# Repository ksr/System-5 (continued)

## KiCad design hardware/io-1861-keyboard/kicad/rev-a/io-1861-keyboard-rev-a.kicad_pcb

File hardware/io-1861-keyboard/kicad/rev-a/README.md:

# io-1861-keyboard-rev-a — KiCad conversion

Generated 2026-10-06 by `tools/eagle_to_kicad_all.py` from the Fusion XML export of the Eagle design `Video` in `hardware/io-1861-keyboard/eagle/rev-a/fusion-export/`. **The Eagle files are the record of what was designed and built; this KiCad project is derived from them and is regenerated from scratch on every run of the tool** (hand edits here will be lost - once a card is edited in KiCad, remove it from the tool's list). This revision was FABRICATED (see `hardware/FABRICATED.md`).

## Files

| File | What it is |
|---|---|
| `io-1861-keyboard-rev-a.kicad_pro` | project; DRC uses OSH Park rules (6 mil track, 5 mil clearance, 10 mil drill, 4 mil annular) as a modern-fab check, not the 2005 fab's rules |
| `io-1861-keyboard-rev-a.kicad_sch` | root sheet; 1 sub-sheet(s) `io-1861-keyboard-rev-a-sheetN.kicad_sch` mirror the Eagle sheets |
| `io-1861-keyboard-rev-a-eagle.kicad_sym` | project symbol library generated from the Eagle libraries used (units = Eagle gates) |
| `io-1861-keyboard-rev-a.kicad_pcb` | the board: 4 copper layers, 47 footprints, 999 track segments, 112 vias; 4 items on unmapped Eagle layers dropped |
| `io-1861-keyboard-rev-a-eagle.pretty/` | project footprint library extracted from the imported board |
| `reports/` | ERC (`erc.json`), DRC (`drc.json`), schematic PDF, board renders (`-top.png`, `-bottom.png`), netlist + `netlist-compare.txt` |

## Proof

Schematic-vs-board netlist comparison (`tools/kicad/compare_netlists.py`: every (reference, pad) partition must be identical): **MATCH (79/79 nets)**

```
  same connectivity, different net name: [('/Sheet 1/-INT', '-INT'), ('/Sheet 1/-MRD', '-MRD'), ('/Sheet 1/CLK', 'CLK'), ('/Sheet 1/DATA', 'DATA'), ('/Sheet 1/DATA0', 'DATA0'), ('/Sheet 1/DATA1', 'DATA1'), ('/Sheet 1/DATA2', 'DATA2'), ('/Sheet 1/DATA3', 'DATA3'), ('/Sheet 1/DATA4', 'DATA4'), ('/Sheet 1/DATA5', 'DATA5'), ('/Sheet 1/DATA6', 'DATA6'), ('/Sheet 1/DATA7', 'DATA7'), ('/Sheet 1/DMA_OUT', 'DMA_OUT'), ('/Sheet 1/EFK', 'EFK'), ('/Sheet 1/EFV', 'EFV'), ('/Sheet 1/IN', 'IN'), ('/Sheet 1/KD0', 'KD0'), ('/Sheet 1/KD1', 'KD1'), ('/Sheet 1/KD2', 'KD2'), ('/Sheet 1/KD3', 'KD3'), ('/Sheet 1/KD4', 'KD4'), ('/Sheet 1/KD5', 'KD5'), ('/Sheet 1/KD6', 'KD6'), ('/Sheet 1/KD7', 'KD7'), ('/Sheet 1/LCLK', 'LCLK'), ('/Sheet 1/N0', 'N0'), ('/Sheet 1/N1', 'N1'), ('/Sheet 1/N2', 'N2'), ('/Sheet 1/OUT', 'OUT'), ('/Sheet 1/PORT1', 'PORT1'), ('/Sheet 1/PORT2', 'PORT2'), ('/Sheet 1/PORT3', 'PORT3'), ('/Sheet 1/PORT4', 'PORT4'), ('/Sheet 1/PORT5', 'PORT5'), ('/Sheet 1/PORT6', 'PORT6'), ('/Sheet 1/PORT7', 'PORT7'), ('/Sheet 1/RESET', 'RESET'), ('/Sheet 1/SC0', 'SC0'), ('/Sheet 1/SC1', 'SC1'), ('/Sheet 1/TPA', 'TPA'), ('/Sheet 1/TPB', 'TPB'), ('Net-(IC1-OSC1)', 'N$19'), ('Net-(IC1-OSC2)', 'N$21'), ('Net-(IC1-RA0)', 'N$3'), ('Net-(IC1-RA1)', 'N$6'), ('Net-(IC1-RA2)', 'N$15'), ('Net-(IC2A-~{Q})', 'N$24'), ('Net-(IC11A-I)', 'N$5'), ('Net-(IC11A-O)', 'N$10'), ('Net-(IC11C-O)', 'N$28'), ('Net-(IC11D-O)', 'N$14'), ('Net-(IC11E-I)', 'N$41'), ('Net-(IC11E-O)', 'N$40'), ('Net-(IC11F-I)', 'N$20'), ('Net-(IC11F-O)', 'N$18'), ('Net-(IC13A-O)', 'N$11'), ('Net-(IC14A-I1)', 'N$13'), ('Net-(IC14A-O)', 'N$12'), ('Net-(IC14C-O)', 'N$26'), ('Net-(IC14D-O)', 'N$39'), ('Net-(IC16A-I1)', 'N$42'), ('Net-(IC16A-O)', 'N$43'), ('Net-(IC16B-O)', 'N$44'), ('Net-(LED1-C)', 'N$22'), ('Net-(LED2-C)', 'N$23'), ('Net-(LED3-C)', 'N$4'), ('Net-(LED4-C)', 'N$25'), ('Net-(LED5-C)', 'N$29'), ('Net-(R13-Pad1)', 'N$9'), ('Net-(U$1-SR)', 'N$16'), ('Net-(U$2--EF4)', 'N$17'), ('Net-(U$3-SYNC)', 'N$7'), ('Net-(U$3-VIDEO)', 'N$8'), ('Net-(U$5-DA)', 'N$27'), ('Net-(U$5-RES1)', 'N$1'), ('Net-(U$5-RES2)', 'N$2'), ('Net-(X1-PE1)', 'N$30')]
```

## Readability

`tools/kicad/sch_overlaps.py` over every sheet: text over text 3, text over a symbol body 6, text crossed by a line 2, items off the drawing frame or on the title block 0. What is left is mostly the Eagle drawing itself (parts placed that close in Eagle) or KiCad drawing pin numbers centred on short pins.

## Residual ERC / DRC

ERC by type: endpoint_off_grid 19, missing_input_pin 4, missing_power_pin 4, missing_unit 4, power_pin_not_driven 1, unconnected_wire_endpoint 17.
`isolated_pin_label` = the converter's per-net global labels (cosmetic); `power_pin_not_driven` / unused-unit notes are the same ones KiCad's own Eagle importer leaves. `unconnected_wire_endpoint` / `pin_not_connected` = wire stubs Eagle leaves bare (mostly net wires ending on a bus, which is drawn as graphics here); since 2026-09-23 the converter no longer hangs a label on every such end (that was most of the label clutter), so they show as KiCad warnings.

DRC by type: lib_footprint_mismatch 2, silk_edge_clearance 1, silk_over_copper 199, silk_overlap 22, text_height 6, text_thickness 6; unconnected items 0; schematic parity 0.
Silk-over-pad and clearance notes reflect the Eagle design as drawn; unconnected items are Eagle airwires (parts the design left unrouted).

Converter: converted: 80 symbols, 408 wires, 85 labels, 79 junctions, 5 bus lines, 27 no-connects

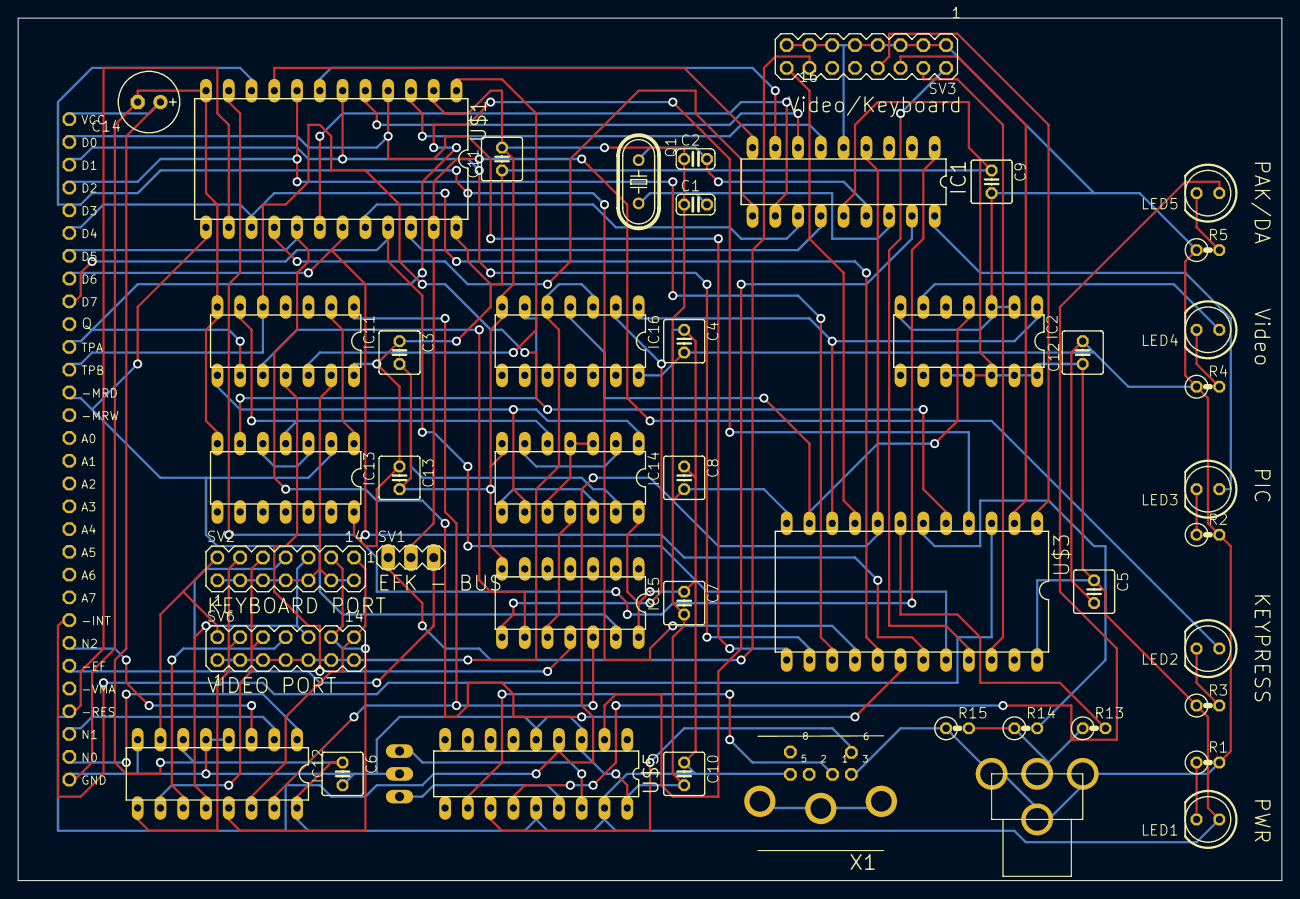
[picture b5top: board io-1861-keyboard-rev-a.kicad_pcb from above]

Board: 4 copper layers, 140.9 x 96.2 mm, 47 parts (0 on the bottom side), 79 nets.

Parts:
C1, C2: C025-024X044
C3, C4, C5, C6, C7, C8, C9, C10, C11, C12, C13: C025-050X050
C14: E2,5-7
IC1: PIC16F84AP; DIL18
IC2: 74LS74N; DIL14
IC11: 74LS04N; DIL14
IC12: 74LS138N; DIL16
IC13: 74S32N; DIL14
IC14, IC15: 74LS00N; DIL14
IC16: 74LS02N; DIL14
LED1, LED2, LED3, LED4, LED5: LED5MM
Q1: HC49U-V
R1, R2, R3, R4, R5, R13, R14, R15: 0207_2V
SV1: MA03-1
SV2, SV6: MA07-2
SV3: MA08-2
U$1: 1852; DIL24
U$2: C30
U$3: CDP1861; DIP24
U$4: RCA
U$5: PAKVI; DIL18
U$6: RESONATOR; MA03-1
X1: M_DIN6

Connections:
-INT: U$2.23, U$3.3
-MRD: IC13.2, IC15.13, U$1.13, U$2.13
CLK: U$5.12, X1.6
DATA: U$5.11, X1.1
DATA0: U$1.4, U$2.2, U$3.13
DATA1: U$1.6, U$2.3, U$3.14
DATA2: U$1.8, U$2.4, U$3.15
DATA3: U$1.10, U$2.5, U$3.16
DATA4: U$1.15, U$2.6, U$3.17
DATA5: U$1.17, U$2.7, U$3.18
DATA6: U$1.19, U$2.8, U$3.19
DATA7: U$1.21, U$2.9, U$3.20
DMA_OUT: SV3.6, U$3.2
EFK: SV1.1, SV3.14
EFV: SV3.16, U$3.9
GND: C1.1, C2.1, C3.2, C4.2, C5.2, C6.2, C7.2, C8.2, C9.2, C10.2, C11.2, C12.2, C13.2, C14.-, IC1.5, IC2.2, IC2.3, IC2.7, IC11.7, IC12.4, IC12.5, IC12.8, IC13.7, IC14.7, IC15.7, IC16.7, R1.2, R2.2, R4.1, R5.1, R15.1, SV3.1, SV3.3, SV3.5, SV3.7, SV3.9, SV3.11, SV3.13, SV3.15, U$1.2, U$1.12, U$2.30, U$3.12, U$4.S1, U$4.S2, U$4.S3, U$5.3, U$5.5, U$5.18, U$6.2, X1.3
IN: IC15.8, IC16.2
KD0: IC1.6, U$1.3
KD1: IC1.7, U$1.5
KD2: IC1.8, U$1.7
KD3: IC1.9, U$1.9
KD4: IC1.10, U$1.16
KD5: IC1.11, U$1.18
KD6: IC1.12, U$1.20
KD7: IC1.13, U$1.22
LCLK: SV3.8, U$3.1
N0: IC12.1, U$2.29
N1: IC12.2, U$2.28
N2: IC12.3, U$2.24
unnamed: U$5.15, U$6.3
unnamed: U$5.16, U$6.1
unnamed: IC1.17, U$5.2
unnamed: LED3.K, R2.1
unnamed: IC11.1, IC12.15, IC15.12
unnamed: IC1.18, LED3.A
unnamed: R14.2, U$3.6
unnamed: R13.2, U$3.7
unnamed: R13.1, R14.1, R15.2, U$4.C1
unnamed: IC11.2, IC13.1
unnamed: IC13.3, IC13.5
unnamed: IC14.3, IC14.4, IC14.10
unnamed: IC14.2, IC14.6
unnamed: IC11.8, IC14.1, IC14.9
unnamed: IC1.1, U$1.11
unnamed: LED2.A, SV1.2, U$1.23
unnamed: SV1.3, U$2.25
unnamed: IC11.12, U$1.1
unnamed: C1.2, IC1.16, Q1.2
unnamed: IC11.13, SV2.1, SV2.3, SV2.5, SV2.7, SV2.9, SV2.11, SV2.13
unnamed: C2.2, IC1.15, Q1.1
unnamed: LED1.K, R1.1
unnamed: LED2.K, R3.2
unnamed: IC2.6, LED4.A
unnamed: LED4.K, R4.2
unnamed: IC14.8, IC14.12
unnamed: LED5.A, U$5.13
unnamed: IC11.6, IC13.4, IC14.5, IC14.13
unnamed: LED5.K, R5.2
unnamed: X1.SH1, X1.SH2, X1.SH3
unnamed: IC14.11, IC15.10
unnamed: IC11.10, IC15.9
unnamed: IC11.11, IC15.11
unnamed: IC16.3, IC16.5, SV6.1, SV6.3, SV6.5, SV6.7, SV6.9, SV6.11, SV6.13
unnamed: IC2.1, IC16.1, U$3.10
unnamed: IC2.4, IC16.4, U$3.11
OUT: IC13.6, IC16.6
PORT1: IC12.14, SV2.14, SV6.14
PORT2: IC12.13, SV2.12, SV6.12
PORT3: IC12.12, SV2.10, SV6.10
PORT4: IC12.11, SV2.8, SV6.8
PORT5: IC12.10, SV2.6, SV6.6
PORT6: IC12.9, SV2.4, SV6.4
PORT7: IC12.7, SV2.2, SV6.2
RESET: IC1.4, U$1.14, U$2.27, U$3.8, U$5.4
SC0: SV3.2, U$3.21
SC1: SV3.4, U$3.22
TPA: IC11.9, U$2.11, U$3.4
TPB: IC11.5, U$2.12, U$3.5
VCC: C3.1, C4.1, C5.1, C6.1, C7.1, C8.1, C9.1, C10.1, C11.1, C12.1, C13.1, C14.+, IC1.14, IC2.10, IC2.11, IC2.12, IC2.13, IC2.14, IC11.14, IC12.6, IC12.16, IC13.14, IC14.14, IC15.14, IC16.14, LED1.A, R3.1, U$1.24, U$2.1, U$3.24, U$5.14, U$5.17, X1.5

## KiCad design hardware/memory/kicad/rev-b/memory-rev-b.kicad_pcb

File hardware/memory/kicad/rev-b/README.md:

# memory-rev-b — KiCad conversion

Generated 2026-10-05 by `tools/eagle_to_kicad_all.py` from the Fusion XML export of the Eagle design `mem3-b` in `hardware/memory/eagle/rev-b/fusion-export/`. **The Eagle files are the record of what was designed and built; this KiCad project is derived from them and is regenerated from scratch on every run of the tool** (hand edits here will be lost - once a card is edited in KiCad, remove it from the tool's list). This revision was FABRICATED (see `hardware/FABRICATED.md`).

## Files

| File | What it is |
|---|---|
| `memory-rev-b.kicad_pro` | project; DRC uses OSH Park rules (6 mil track, 5 mil clearance, 10 mil drill, 4 mil annular) as a modern-fab check, not the 2005 fab's rules |
| `memory-rev-b.kicad_sch` | root sheet; 1 sub-sheet(s) `memory-rev-b-sheetN.kicad_sch` mirror the Eagle sheets |
| `memory-rev-b-eagle.kicad_sym` | project symbol library generated from the Eagle libraries used (units = Eagle gates) |
| `memory-rev-b.kicad_pcb` | the board: 4 copper layers, 48 footprints, 1547 track segments, 170 vias; 2 items on unmapped Eagle layers dropped |
| `memory-rev-b-eagle.pretty/` | project footprint library extracted from the imported board |
| `reports/` | ERC (`erc.json`), DRC (`drc.json`), schematic PDF, board renders (`-top.png`, `-bottom.png`), netlist + `netlist-compare.txt` |

## Proof

Schematic-vs-board netlist comparison (`tools/kicad/compare_netlists.py`: every (reference, pad) partition must be identical): **MATCH (88/88 nets)**

```
  same connectivity, different net name: [('/Sheet 1/BUFFADDR0', 'BUFFADDR0'), ('/Sheet 1/BUFFADDR1', 'BUFFADDR1'), ('/Sheet 1/BUFFADDR2', 'BUFFADDR2'), ('/Sheet 1/BUFFADDR3', 'BUFFADDR3'), ('/Sheet 1/BUFFADDR4', 'BUFFADDR4'), ('/Sheet 1/BUFFADDR5', 'BUFFADDR5'), ('/Sheet 1/BUFFADDR6', 'BUFFADDR6'), ('/Sheet 1/BUFFADDR7', 'BUFFADDR7'), ('/Sheet 1/BUFFADDR8', 'BUFFADDR8'), ('/Sheet 1/BUFFADDR9', 'BUFFADDR9'), ('/Sheet 1/BUFFADDR10', 'BUFFADDR10'), ('/Sheet 1/BUFFADDR11', 'BUFFADDR11'), ('/Sheet 1/BUFFADDR12', 'BUFFADDR12'), ('/Sheet 1/BUFFADDR13', 'BUFFADDR13'), ('/Sheet 1/BUFFADDR14', 'BUFFADDR14'), ('/Sheet 1/BUFFADDR15', 'BUFFADDR15'), ('/Sheet 1/BUSDATA0', 'BUSDATA0'), ('/Sheet 1/BUSDATA1', 'BUSDATA1'), ('/Sheet 1/BUSDATA2', 'BUSDATA2'), ('/Sheet 1/BUSDATA3', 'BUSDATA3'), ('/Sheet 1/BUSDATA4', 'BUSDATA4'), ('/Sheet 1/BUSDATA5', 'BUSDATA5'), ('/Sheet 1/BUSDATA6', 'BUSDATA6'), ('/Sheet 1/BUSDATA7', 'BUSDATA7'), ('/Sheet 1/RD', 'RD'), ('/Sheet 1/WR', 'WR'), ('Net-(IC1-~{CE})', 'N$34'), ('Net-(IC2-D0)', 'N$18'), ('Net-(IC2-D1)', 'N$17'), ('Net-(IC2-D2)', 'N$16'), ('Net-(IC2-D3)', 'N$15'), ('Net-(IC2-D4)', 'N$6'), ('Net-(IC2-D5)', 'N$4'), ('Net-(IC2-D6)', 'N$3'), ('Net-(IC2-D7)', 'N$2'), ('Net-(IC4-D0)', 'N$33'), ('Net-(IC4-D1)', 'N$30'), ('Net-(IC4-D2)', 'N$29'), ('Net-(IC4-D3)', 'N$28'), ('Net-(IC4-D4)', 'N$24'), ('Net-(IC4-D5)', 'N$23'), ('Net-(IC4-D6)', 'N$22'), ('Net-(IC4-D7)', 'N$21'), ('Net-(IC6-CLK)', 'N$5'), ('Net-(IC7A-I)', 'N$7'), ('Net-(IC7B-I)', 'N$8'), ('Net-(IC7C-I)', 'N$9'), ('Net-(IC7D-I)', 'N$10'), ('Net-(IC7E-I)', 'N$11'), ('Net-(IC7F-I)', 'N$12'), ('Net-(IC8A-I)', 'N$13'), ('Net-(IC8B-I)', 'N$14'), ('Net-(IC8C-I)', 'N$26'), ('Net-(IC8D-I)', 'N$25'), ('Net-(IC10A-O)', 'N$58'), ('Net-(IC10B-I0)', 'N$51'), ('Net-(IC10B-O)', 'N$62'), ('Net-(IC10C-I0)', 'N$36'), ('Net-(IC10C-O)', 'N$19'), ('Net-(IC10D-I0)', 'N$49'), ('Net-(IC10D-O)', 'N$57'), ('Net-(IC13-D0)', 'N$46'), ('Net-(IC13-D1)', 'N$43'), ('Net-(IC13-D2)', 'N$42'), ('Net-(IC13-D3)', 'N$41'), ('Net-(IC13-D4)', 'N$40'), ('Net-(IC13-D5)', 'N$39'), ('Net-(IC13-D6)', 'N$38'), ('Net-(IC13-D7)', 'N$45'), ('Net-(IC13-G)', 'N$20'), ('Net-(IC14A-I0)', 'N$27'), ('Net-(IC14A-O)', 'N$52'), ('Net-(IC14B-I1)', 'N$50'), ('Net-(IC15-D0)', 'N$68'), ('Net-(IC15-D1)', 'N$67'), ('Net-(IC15-D2)', 'N$66'), ('Net-(IC15-D3)', 'N$65'), ('Net-(IC15-D4)', 'N$64'), ('Net-(IC15-D5)', 'N$63'), ('Net-(IC15-D6)', 'N$60'), ('Net-(IC15-D7)', 'N$55'), ('Net-(LED1-C)', 'N$1'), ('Net-(LED2-C)', 'N$59'), ('Net-(LED3-C)', 'N$61'), ('Net-(LED4-C)', 'N$32'), ('Net-(LED5-C)', 'N$56')]
```

## Readability

`tools/kicad/sch_overlaps.py` over every sheet: text over text 16, text over a symbol body 4, text crossed by a line 1, items off the drawing frame or on the title block 0. What is left is mostly the Eagle drawing itself (parts placed that close in Eagle) or KiCad drawing pin numbers centred on short pins.

## Residual ERC / DRC

ERC by type: endpoint_off_grid 29, unconnected_wire_endpoint 33.
`isolated_pin_label` = the converter's per-net global labels (cosmetic); `power_pin_not_driven` / unused-unit notes are the same ones KiCad's own Eagle importer leaves. `unconnected_wire_endpoint` / `pin_not_connected` = wire stubs Eagle leaves bare (mostly net wires ending on a bus, which is drawn as graphics here); since 2026-09-23 the converter no longer hangs a label on every such end (that was most of the label clutter), so they show as KiCad warnings.

DRC by type: silk_over_copper 199, silk_overlap 174; unconnected items 0; schematic parity 0.
Silk-over-pad and clearance notes reflect the Eagle design as drawn; unconnected items are Eagle airwires (parts the design left unrouted).

Converter: converted: 84 symbols, 511 wires, 151 labels, 113 junctions, 18 bus lines, 27 no-connects

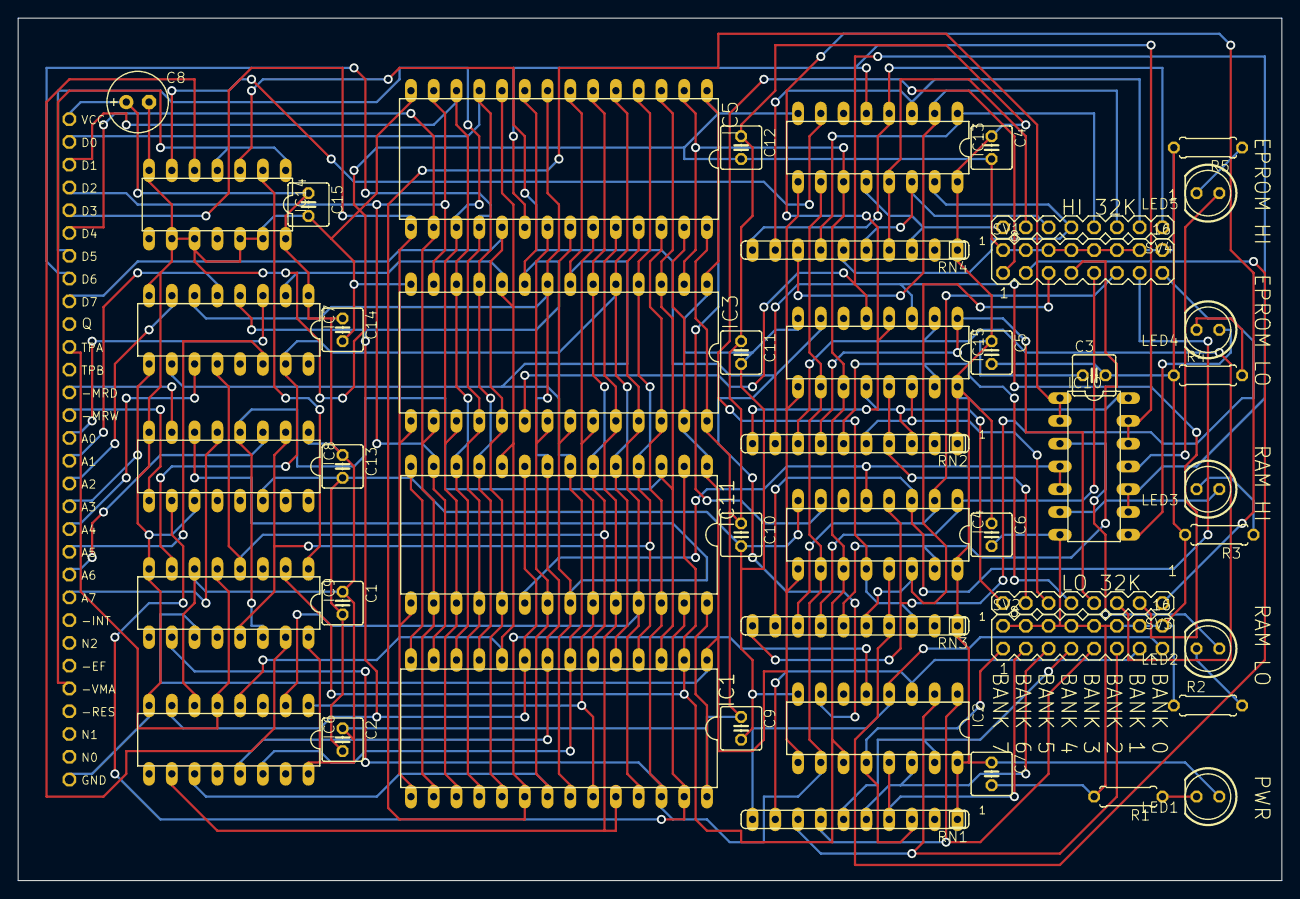
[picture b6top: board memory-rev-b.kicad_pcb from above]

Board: 4 copper layers, 140.9 x 96.2 mm, 48 parts (0 on the bottom side), 88 nets.

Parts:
C1, C2, C3, C4, C5, C6, C7, C9, C10, C11, C12, C13, C14, C15: .1; C025-050X050
C8: 10.0; E2,5-7
IC1, IC11: 62256; DIL28-6
IC2, IC4, IC13, IC15: 74LS151N; DIL16
IC3, IC5: 27256; DIL28
IC6, IC9: 4042N; DIL16
IC7, IC8: 4050N; DIL16
IC10: 74LS00N; DIL14
IC14: 74LS32N; DIL14
LED1, LED2, LED3, LED4, LED5: LED5MM
R1, R2, R3, R4, R5: 470; 0207_7
RN1, RN2, RN3, RN4: SIL10
SV1, SV2: MA08-2
SV3, SV4: MA08-1
U$1: C30

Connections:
BUFFADDR0: IC1.10, IC3.10, IC5.10, IC6.4, IC7.2, IC11.10
BUFFADDR1: IC1.9, IC3.9, IC5.9, IC6.7, IC7.4, IC11.9
BUFFADDR2: IC1.8, IC3.8, IC5.8, IC6.13, IC7.6, IC11.8
BUFFADDR3: IC1.7, IC3.7, IC5.7, IC6.14, IC7.10, IC11.7
BUFFADDR4: IC1.6, IC3.6, IC5.6, IC7.12, IC9.4, IC11.6
BUFFADDR5: IC1.5, IC3.5, IC5.5, IC7.15, IC9.7, IC11.5
BUFFADDR6: IC1.4, IC3.4, IC5.4, IC8.2, IC9.13, IC11.4
BUFFADDR7: IC1.3, IC3.3, IC5.3, IC8.4, IC9.14, IC11.3
BUFFADDR8: IC1.25, IC3.25, IC5.25, IC6.2, IC11.25
BUFFADDR9: IC1.24, IC3.24, IC5.24, IC6.10, IC11.24
BUFFADDR10: IC1.21, IC3.21, IC5.21, IC6.11, IC11.21
BUFFADDR11: IC1.23, IC3.23, IC5.23, IC6.1, IC11.23
BUFFADDR12: IC1.2, IC2.11, IC3.2, IC4.11, IC5.2, IC9.2, IC11.2, IC13.11, IC15.11
BUFFADDR13: IC1.26, IC2.10, IC3.26, IC4.10, IC5.26, IC9.10, IC11.26, IC13.10, IC15.10
BUFFADDR14: IC1.1, IC2.9, IC3.27, IC4.9, IC5.27, IC9.11, IC11.1, IC13.9, IC15.9
BUFFADDR15: IC9.1, IC14.2
BUSDATA0: IC1.11, IC3.11, IC5.11, IC11.11, U$1.2
BUSDATA1: IC1.12, IC3.12, IC5.12, IC11.12, U$1.3
BUSDATA2: IC1.13, IC3.13, IC5.13, IC11.13, U$1.4
BUSDATA3: IC1.15, IC3.15, IC5.15, IC11.15, U$1.5
BUSDATA4: IC1.16, IC3.16, IC5.16, IC11.16, U$1.6
BUSDATA5: IC1.17, IC3.17, IC5.17, IC11.17, U$1.7
BUSDATA6: IC1.18, IC3.18, IC5.18, IC11.18, U$1.8
BUSDATA7: IC1.19, IC3.19, IC5.19, IC11.19, U$1.9
GND: C1.2, C2.2, C3.2, C4.2, C5.2, C6.2, C7.2, C8.-, C9.2, C10.2, C11.2, C12.2, C13.2, C14.2, C15.2, IC1.14, IC2.8, IC3.1, IC3.14, IC4.8, IC5.1, IC5.14, IC6.8, IC7.8, IC8.8, IC8.11, IC8.14, IC9.8, IC10.7, IC11.14, IC13.8, IC14.7, IC14.9, IC14.10, IC14.12, IC14.13, IC15.8, R1.2, R2.1, R3.2, R4.1, R5.2, SV1.2, SV1.4, SV1.6, SV1.8, SV1.10, SV1.12, SV1.14, SV1.16, SV2.2, SV2.4, SV2.6, SV2.8, SV2.10, SV2.12, SV2.14, SV2.16, U$1.30
unnamed: LED1.K, R1.1
unnamed: IC2.12, RN1.3, SV2.1
unnamed: IC2.13, RN1.4, SV2.3
unnamed: IC2.14, RN1.5, SV2.5
unnamed: IC6.5, IC9.5, U$1.11
unnamed: IC2.15, RN1.6, SV2.7
unnamed: IC7.3, U$1.15
unnamed: IC7.5, U$1.16
unnamed: IC7.7, U$1.17
unnamed: IC7.9, U$1.18
unnamed: IC7.11, U$1.19
unnamed: IC7.14, U$1.20
unnamed: IC8.3, U$1.21
unnamed: IC8.5, U$1.22
unnamed: IC2.1, RN1.7, SV2.9
unnamed: IC2.2, RN1.8, SV2.11
unnamed: IC2.3, RN1.9, SV2.13
unnamed: IC2.4, RN1.10, SV2.15
unnamed: IC10.8, LED4.A
unnamed: IC4.7, IC13.7, IC14.6
unnamed: IC4.12, RN3.3, SV1.1
unnamed: IC4.13, RN3.4, SV1.3
unnamed: IC4.14, RN3.5, SV1.5
unnamed: IC4.15, RN3.6, SV1.7
unnamed: IC8.9, U$1.14
unnamed: IC8.7, U$1.13
unnamed: IC14.1, IC14.4, U$1.26
unnamed: IC4.1, RN3.7, SV1.9
unnamed: IC4.2, RN3.8, SV1.11
unnamed: IC4.3, RN3.9, SV1.13
unnamed: LED4.K, R4.2
unnamed: IC4.4, RN3.10, SV1.15
unnamed: IC1.20, IC2.5, IC10.1, IC10.2
unnamed: IC3.20, IC10.9, IC10.10, IC15.5
unnamed: IC13.13, RN4.4, SV4.7
unnamed: IC13.14, RN4.5, SV4.6
unnamed: IC13.15, RN4.6, SV4.5
unnamed: IC13.1, RN4.7, SV4.4
unnamed: IC13.2, RN4.8, SV4.3
unnamed: IC13.3, RN4.9, SV4.2
unnamed: IC13.12, RN4.3, SV4.8
unnamed: IC13.4, RN4.10, SV4.1
unnamed: IC5.20, IC10.12, IC10.13, IC13.5
unnamed: IC9.15, IC14.5
unnamed: IC4.5, IC10.4, IC10.5, IC11.20
unnamed: IC2.7, IC14.3, IC15.7
unnamed: IC15.12, RN2.3, SV3.8
unnamed: LED5.K, R5.1
unnamed: IC10.11, LED5.A
unnamed: IC10.3, LED2.A
unnamed: LED2.K, R2.2
unnamed: IC15.13, RN2.4, SV3.7
unnamed: LED3.K, R3.1
unnamed: IC10.6, LED3.A
unnamed: IC15.14, RN2.5, SV3.6
unnamed: IC15.15, RN2.6, SV3.5
unnamed: IC15.1, RN2.7, SV3.4
unnamed: IC15.2, RN2.8, SV3.3
unnamed: IC15.3, RN2.9, SV3.2
unnamed: IC15.4, RN2.10, SV3.1
RD: IC1.22, IC3.22, IC5.22, IC8.6, IC11.22
VCC: C1.1, C2.1, C3.1, C4.1, C5.1, C6.1, C7.1, C8.+, C9.1, C10.1, C11.1, C12.1, C13.1, C14.1, C15.1, IC1.28, IC2.16, IC3.28, IC4.16, IC5.28, IC6.6, IC6.16, IC7.1, IC8.1, IC9.6, IC9.16, IC10.14, IC11.28, IC13.16, IC14.14, IC15.16, LED1.A, RN1.1, RN2.1, RN3.1, RN4.1, U$1.1
WR: IC1.27, IC8.10, IC11.27

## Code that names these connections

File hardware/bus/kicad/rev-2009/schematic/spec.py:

# Author: Claude (Anthropic) for Ken Rother's System-5 project, 2026-10-26
"""The 2009 bus backplane, redrawn by tools/kicad/sch/gen_schematic.py from ../reports/netlist.net.
Theory: docs/manual/bus.md."""
PROJ = "bus-rev-2009-schematic"
TITLE = "System-5 bus backplane (2009)"
SUBTITLE = "Six 36-pin slots: the 30-pin System-5 bus with -EF1-3 above and -INP, -OUT, EXP below; power on X1"
THEORY = "The bus: docs/manual/bus.md; Eagle source: hardware/bus/eagle/rev-2009 (from Eagle's 2009 backups)"
DATE = "2026-10-26"
REV = "2009"
BUSREF = "U$1"
RENAME = {"5V": "VCC"}                    # the 2009 drawing names the supply net 5V; KiCad's power symbol is VCC
ROOT_NOTE = "Redrawn 2026-10-26 from the board netlist; proven pin for pin against it (gen_schematic.py)."
SHEETS = [
    ("slots", "Slots", "SIX 36-PIN SLOTS, EVERY PIN BUSSED (X1, THE POWER CONNECTOR, IS NOT WIRED)",
     [], (["U$1", "U$2", "U$3", "U$4", "U$5", "U$6", "X1"], "top"),
     "Every slot carries the same 36 lines, pin for pin: -EF1, -EF2, -EF3, then the 30-pin System-5 bus (VCC, D0-D7, Q,\n"
     "TPA, TPB, -MRD, -MRW, A0-A7, -INT, N2, -EF, -VMA, -RESET, N1, N0, GND), then -INP, -OUT and EXP. A 30-pin card\n"
     "plugs into the middle 30: pins 1-30 are the System-5 bus pin for pin, 31-33 = -EF1-3, 34-36 = -INP, -OUT, EXP.\n"
     "X1 (power) is on no net in the drawing; on the copper its pin 2 touches GND and pin 1 nothing (the +5V track stops short)."),
    ("power", "Power", "POWER", [], None, "VCC (the drawing's 5V) and GND: slot pins 1 and 30. X1: on the copper pin 2 touches GND, pin 1 nothing (the +5V track stops short of it)."),
]
